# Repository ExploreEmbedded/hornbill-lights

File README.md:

# hornbill-lights
Firmware and App for controlling RGB LED lights with the Hornbill ESP32 Platform

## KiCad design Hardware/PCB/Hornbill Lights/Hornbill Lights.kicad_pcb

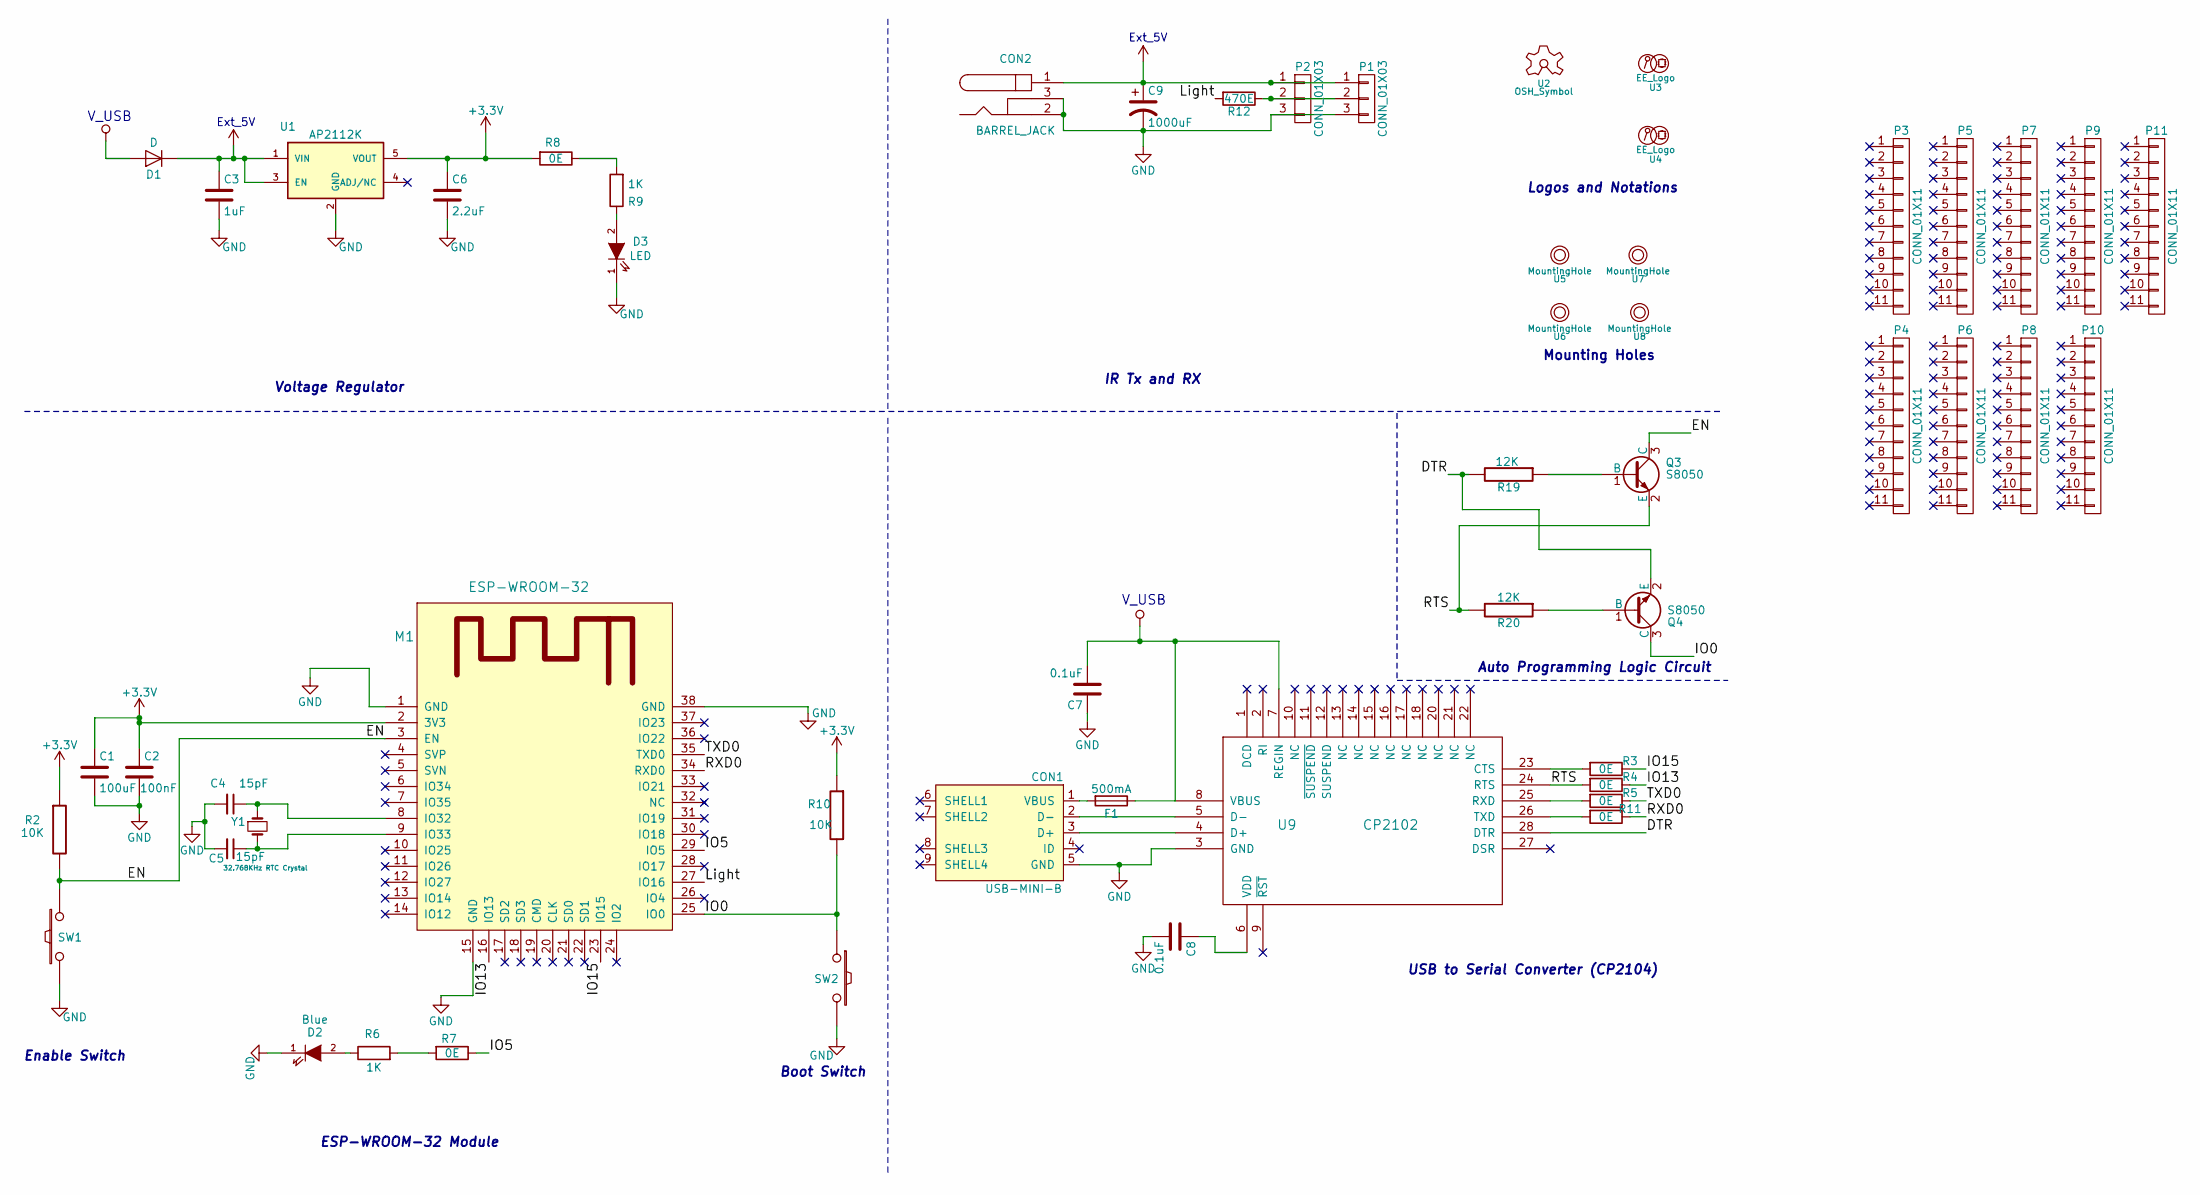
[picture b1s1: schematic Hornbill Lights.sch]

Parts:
C1: 100uF; C_1206
C2: 100nF; C_0603
C3: 1uF; C_0603
C4, C5: 15pF; C_0603
C6: 2.2uF; C_0603
C7, C8: 0.1uF; C_0603
C9: 1000uF; CP_Radial_Tantal_D10.5mm_P5.00mm
CON1: USB-MINI-B; USB_Micro-B_SMD_NEW_1
CON2: BARREL_JACK
D1: D; SOD-80_diode_1
D2: Blue; LED-0603_NEW
D3: LED; LED-0603_NEW
F1: 500mA; Fuse_500mA
M1: ESP-WROOM-32; ESP-32S
P1, P2: CONN_01X03; Pin_Header_Straight_1x03_Pitch2.54mm
P3, P4, P5, P6, P7, P8, P9, P10, P11: CONN_01X11; Pin_Header_Straight_1x11_Pitch2.54mm
Q3, Q4: S8050; SOT-23
R2, R10: 10K; R_0603
R3, R4, R5, R7, R8, R11: 0E; R_0603
R6, R9: 1K; R_0603
R12: 470E; R_0603
R19, R20: 12K; R_0603
SW1, SW2: SW_PUSH; smd_push2_New
U1: AP2112K; SOT-23-5
U2: OSH_Symbol; Logo_silk_OSHW_6x6mm
U3: EE_Logo; Hornbill Lights
U4: EE_Logo; Logo_8
U5, U6, U7, U8: MountingHole; MountingHole_2.5mm
U9: CP2102; cp2102_xl2
Y1: 32.768KHz RTC Crystal; SMD_RTC_Crstl

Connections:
+3V3: C1.1, C2.1, C6.1, M1.2 (3V3), R2.1, R8.2, R10.1, U1.5 (VOUT)
+5V: C3.1, C9.1, CON2.1, D1.1 (K), P1.1, P2.1, U1.1 (VIN), U1.3 (EN)
/DTR: Q4.2 (E), R19.2, U9.28 (DTR)
/EN: M1.3 (EN), Q3.3 (C), R2.2, SW1.1
/IO0: M1.25 (IO0), Q4.3 (C), R10.2, SW2.1
/IO5: M1.29 (IO5), R7.1
/IO13: M1.16 (IO13), R4.1
/IO15: M1.23 (IO15), R3.1
/Light: M1.27 (IO16), R12.2
/RTS: Q3.2 (E), R4.2, R20.2, U9.24 (RTS)
/RXD0: M1.34 (RXD0), R11.1
/TXD0: M1.35 (TXD0), R5.1
GND: C1.2, C2.2, C3.2, C4.2, C5.2, C6.2, C7.1, C8.2, C9.2, CON1.5 (GND), CON2.2, CON2.3, D2.1 (K), D3.1 (K), M1.1 (GND), M1.15 (GND), M1.38 (GND), P1.3, P2.3, SW1.2, SW2.2, U1.2 (GND), U9.3 (GND)
unnamed: C4.1, M1.8 (IO32), Y1.1
unnamed: C5.1, M1.9 (IO33), Y1.2
unnamed: C8.1, U9.6 (VDD)
unnamed: CON1.1 (VBUS), F1.2
unnamed: CON1.2 (D-), U9.5 (D-)
unnamed: CON1.3 (D+), U9.4 (D+)
unnamed: D2.2 (A), R6.1
unnamed: D3.2 (A), R9.1
unnamed: P1.2, P2.2, R12.1
unnamed: Q3.1 (B), R19.1
unnamed: Q4.1 (B), R20.1
unnamed: R3.2, U9.23 (CTS)
unnamed: R5.2, U9.25 (RXD)
unnamed: R6.2, R7.2
unnamed: R8.1, R9.2
unnamed: R11.2, U9.26 (TXD)
VCC: C7.2, D1.2 (A), F1.1, U9.7 (REGIN), U9.8 (VBUS)

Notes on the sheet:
Logos and Notations
Enable Switch
IR Tx and RX
Boot Switch
V_USB
Ext_5V
Voltage Regulator
Auto Programming Logic Circuit
ESP-WROOM-32 Module
USB to Serial Converter (CP2104)
Mounting Holes

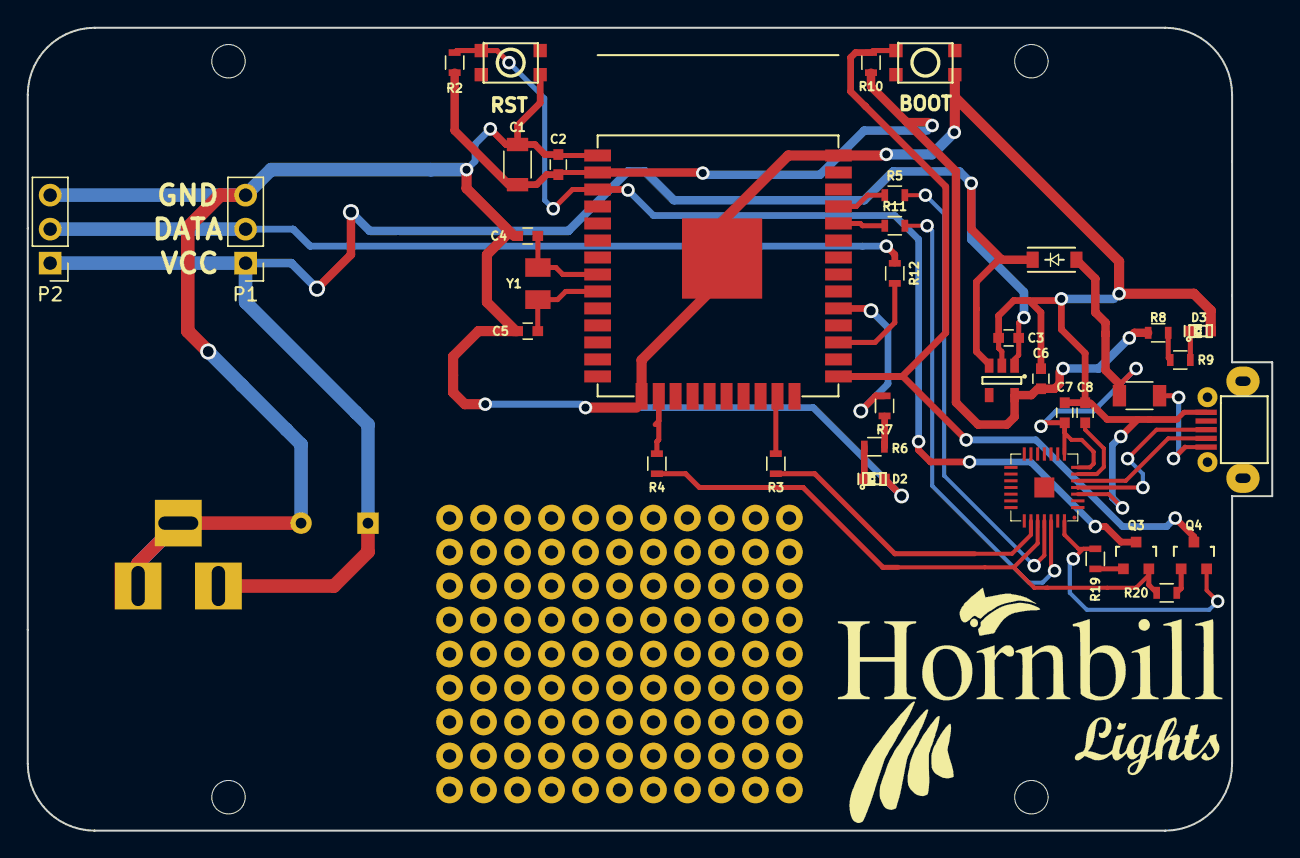
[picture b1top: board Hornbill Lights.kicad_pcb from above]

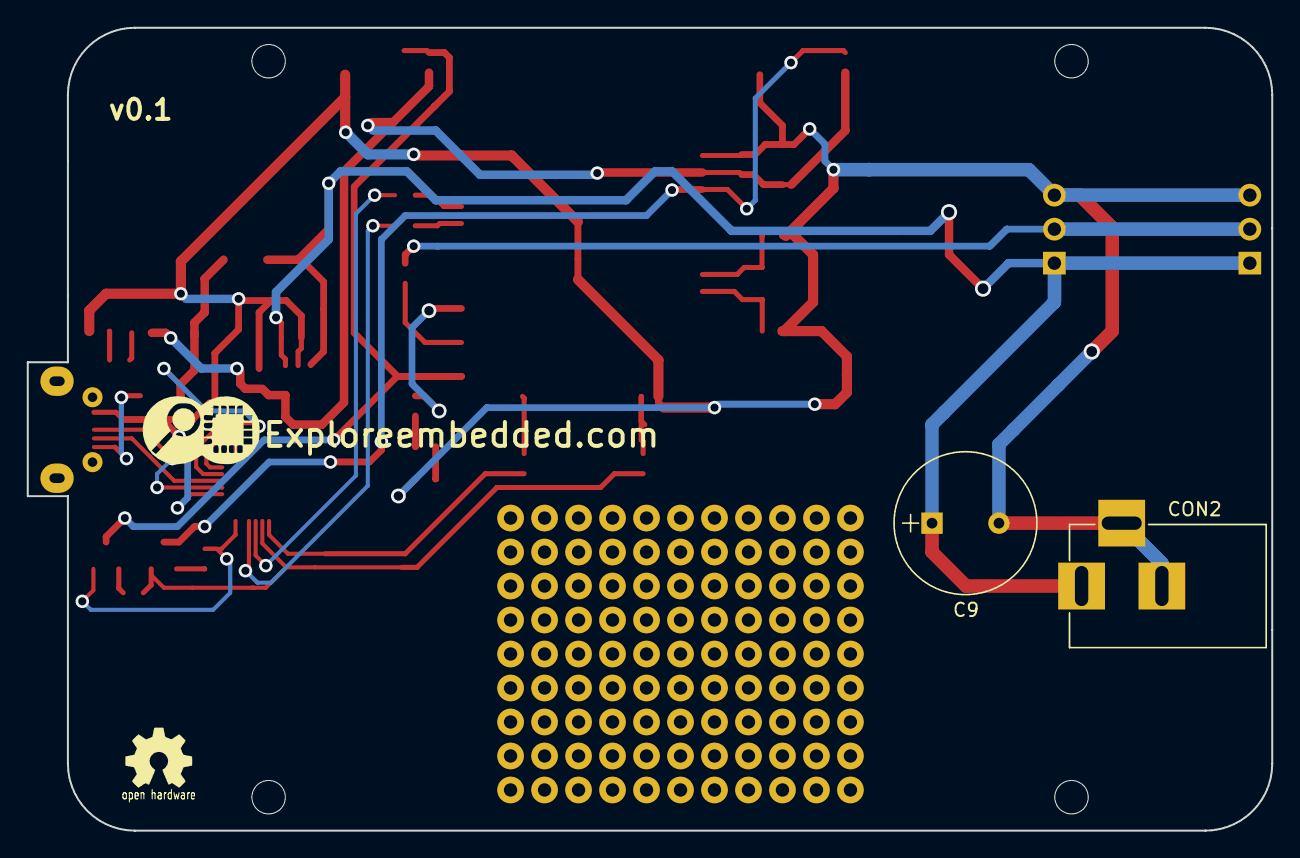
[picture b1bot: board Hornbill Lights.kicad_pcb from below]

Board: 2 copper layers, 93.0 x 60.0 mm, 54 parts (4 on the bottom side), 30 nets.

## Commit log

2017-03-06 test version for controlling WS2812, seperated ble and ws2812 code in seperate files. Lights glow now from main, need to figure out a way to expose ble_receive event and then drive pixels
2017-03-08 firmware and app for hornbill lights, code requires cleanup
2017-05-22 Added PCB Files
2017-05-22 PCB Layout Updated
2017-05-23 Added protype pads
2017-05-23 Gerber data generated for v0.1
2017-07-22 changes to support latest esp-idf skd
2017-07-25 display name and code clean up
